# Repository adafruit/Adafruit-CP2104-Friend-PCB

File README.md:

## Adafruit CP2104 Friend PCB

<a href="http://www.adafruit.com/products/3309"><br/>
Click here to purchase one from the Adafruit shop</a>

PCB files for the Adafruit CP2104 Friend. Format is EagleCAD schematic and board layout
* https://www.adafruit.com/product/3309

### Description

Long gone are the days of parallel ports and serial ports. Now the USB port reigns supreme! But USB is hard, and you just want to transfer your every-day serial data from a microcontroller to computer. What now? Enter the Adafruit CP2104 Friend!

This is a high-quality CP2104 USB-Serial chip that can upload code at a blistering 2Mbit/s for fast development time. It also has auto-reset for Arduino/ATmega328 boards so no noodling with pins and reset button pressings. The CP2104 has better driver support than the CH340 and can do very high speeds, and variable speeds without stability issues. Compared to the FT232RL and FT231X, the CP2104 has the same capabilities or better, at a great price! It even has the RX/TX LEDs to help you debug your data, they'll blink when the chip receives/transmits data.

By default, we've set it up so that it matches our FTDI cables. The 6th pin is RTS, the power wire is +5V and the signal levels are 3.3V (they are 5V compliant, and should work in the vast majority of 3.3V and 5V signal systems). Works excellently with any Arduino, ESP8266, ESP32 or any other microcontroller that uses an 'FTDI port' for communications and upload. You can also purchase a 6-pin extension cable from us, which will let you rearrange the wire order.

There's also a full collection of all the modem control pins you may need on the side, in case you need the DTR, RI, DSR, etc. pins.

### License

Adafruit invests time and resources providing this open source design, please support Adafruit and open-source hardware by purchasing products from [Adafruit](https://www.adafruit.com)!

Designed by Limor Fried/Ladyada for Adafruit Industries.

Creative Commons Attribution/Share-Alike, all text above must be included in any redistribution. See license.txt for additional details.

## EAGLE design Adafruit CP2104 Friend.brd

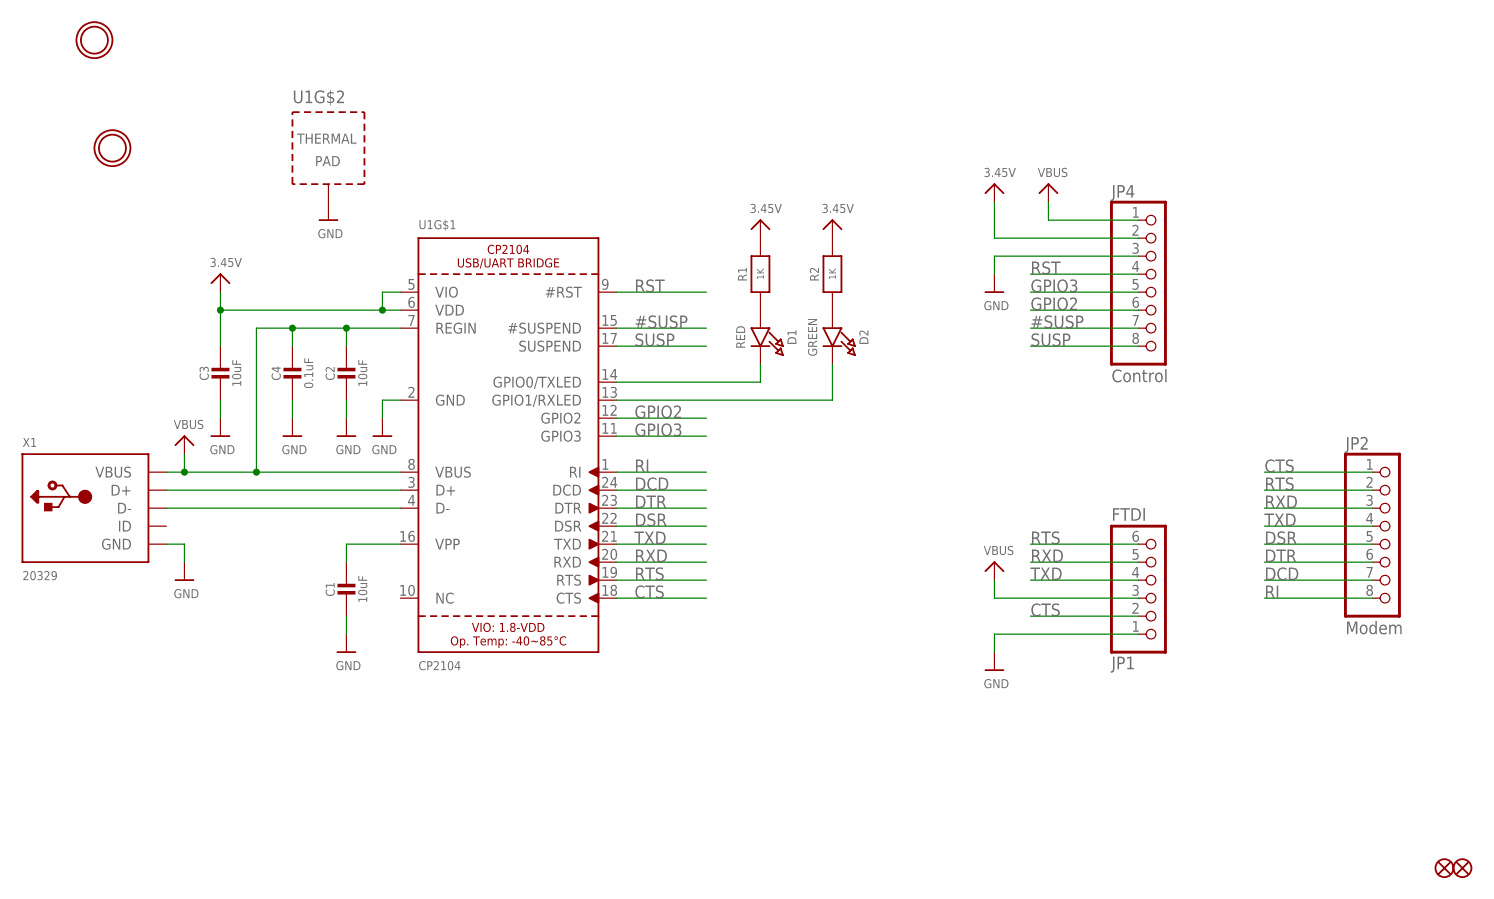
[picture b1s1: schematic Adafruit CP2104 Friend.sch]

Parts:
C1, C2, C3: 10uF; 0805-NO
C4: 0.1uF; 0805-NO
D1: RED; CHIPLED_0805_NOOUTLINE
D2: GREEN; CHIPLED_0805_NOOUTLINE
FID1, FID2: FIDUCIAL""; FIDUCIAL_1MM
JP1: FTDI; 1X06_ROUND_76
JP2: Modem; 1X08_ROUND_70
JP4: Control; 1X08_ROUND_70
R1, R2: 1K; 0805-NO
U1: CP2104; QFN24_4MM_SMSC
U$18, U$19: MOUNTINGHOLE2.0; MOUNTINGHOLE_2.0_PLATED
X1: 20329; 4UCONN_20329_V2

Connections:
3.3V: C3.1, JP4.2, R1.2, R2.2, U1.5 (VIO), U1.6 (VDD)
#SUSP: JP4.7, U1.15 (#SUSPEND)
CTS: JP1.2, JP2.1, U1.18 (CTS)
DCD: JP2.7, U1.24 (DCD)
DSR: JP2.5, U1.22 (DSR)
DTR: JP2.6, U1.23 (DTR)
GND: C1.2, C2.2, C3.2, C4.2, JP1.1, JP4.3, U1.2 (GND), U1.THERM (TP), X1.BASE@1 (GND), X1.BASE@2 (GND), X1.GND, X1.SPRT@1 (GND), X1.SPRT@2 (GND), X1.SPRT@3 (GND), X1.SPRT@4 (GND)
GPIO2: JP4.6, U1.12 (GPIO2)
GPIO3: JP4.5, U1.11 (GPIO3)
unnamed: D1.A, R1.1
unnamed: U1.3 (D+), X1.D+
unnamed: U1.4 (D-), X1.D-
unnamed: C1.1, U1.16 (VPP)
unnamed: D2.A, R2.1
unnamed: D1.C, U1.14 (GPIO0/TXLED)
unnamed: D2.C, U1.13 (GPIO1/RXLED)
RI: JP2.8, U1.1 (RI)
RST: JP4.4, U1.9 (#RST)
RTS: JP1.6, JP2.2, U1.19 (RTS)
RXD: JP1.5, JP2.3, U1.20 (RXD)
SUSP: JP4.8, U1.17 (SUSPEND)
TXD: JP1.4, JP2.4, U1.21 (TXD)
VBUS: C2.1, C4.1, JP1.3, JP4.1, U1.7 (REGIN), U1.8 (VBUS), X1.VBUS

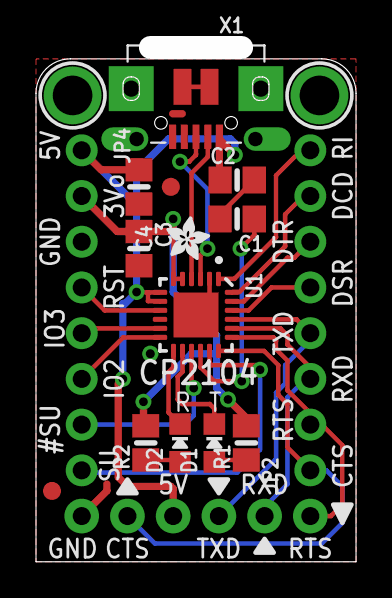
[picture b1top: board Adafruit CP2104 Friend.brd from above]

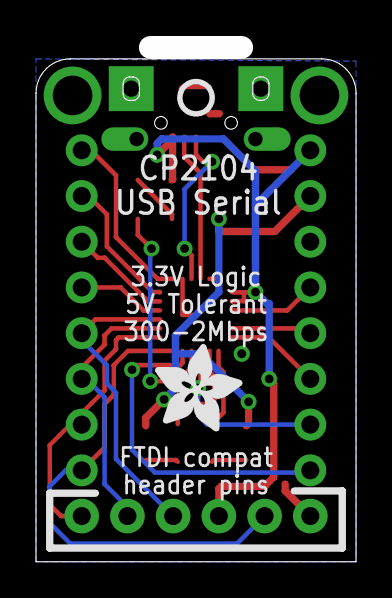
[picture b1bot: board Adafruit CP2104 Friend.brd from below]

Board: 2 copper layers, 16.5 x 27.9 mm, 20 parts (2 on the bottom side), 23 nets.

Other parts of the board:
U$8: ADAFRUIT_2.5MM
U$17: PCBFEAT-REV-040
U$22: ADAFRUIT_5MM

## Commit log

2016-12-19 init
2016-12-20 changed PID

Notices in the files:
parts and their libraries:
microbuilder: This work is placed in the public domain, and may be freely used for commercial and non-commercial work with the following conditions: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
